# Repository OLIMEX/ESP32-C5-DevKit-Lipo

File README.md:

# ESP32-C5-DevKit-Lipo
Dual band 2.4Ghz and 5Ghz WiFi 6, Bluetooth 5 LE, Zigbee, Thread, Matter development board UEXT, USB programming, USB JTAG and LiPo battery UPS

https://www.olimex.com/Products/IoT/ESP32-C5/ESP32-C5-DevKit-Lipo/open-source-hardware

Features:

* 32 bit RISC-V processor 240Mhz
* Dual-Band Wi-Fi (2.4 GHz + 5 GHz)
* Bluetooth 5, Zigbee, Thread, Matter
* 8 MB Flash + 4 MB RAM
* UEXT connector
* USB-C (Power & Debug)
* USB-C JTAG
* Boot & Reset buttons
* Extension connector
* 0.9" (22.86 mm) space between the headers
* LiPo UPS charger & step-up converter
* Status LEDs
* Two mouting holes
* Dimensions 53x25mm

## Licenses

* Hardware is released under CERN Open Hardware Licence Version 2 - Strongly Reciprocal, all silkscreen credits to Olimex should remain;
* Software is released under MIT Licensee
* Documentation is released under CC BY-SA 4.0

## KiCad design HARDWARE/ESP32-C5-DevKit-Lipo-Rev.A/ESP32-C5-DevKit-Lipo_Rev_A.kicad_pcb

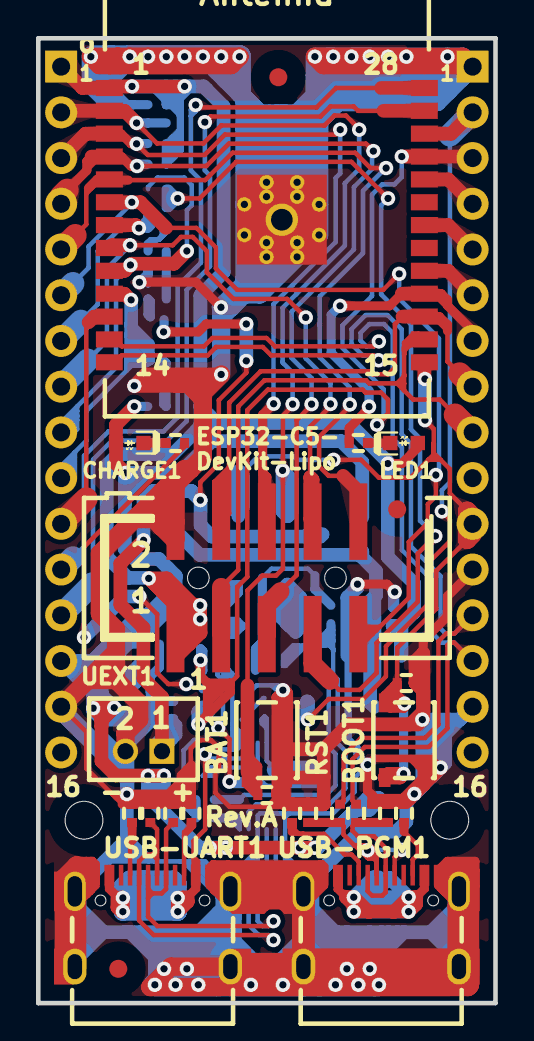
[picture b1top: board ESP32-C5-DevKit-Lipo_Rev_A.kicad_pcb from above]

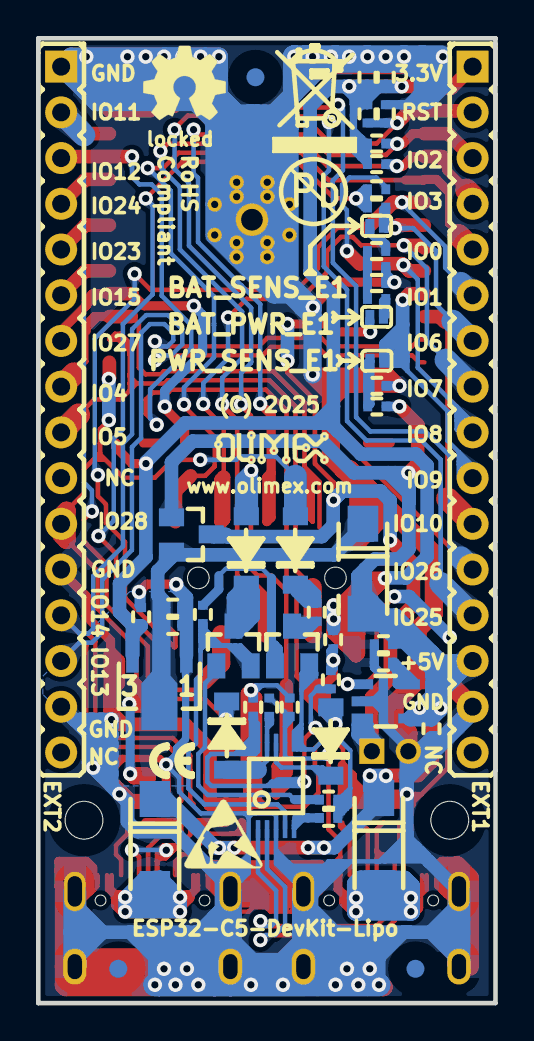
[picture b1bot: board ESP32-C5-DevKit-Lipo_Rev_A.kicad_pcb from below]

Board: 2 copper layers, 25.4 x 53.6 mm, 86 parts (56 on the bottom side), 58 nets.

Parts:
BAT1: DW02S; LIPO_BAT_VERTICAL_DW02S
BAT_PWR_E1: Opened; SJ_1_SMALLER
BAT_SENS_E1: Opened; SJ_1_SMALLER
BOOT1: YTS-A016-X
C1, C2, C7, C10, C12: 10uF/6.3V/20%/X5R/C0402; C_0402_5MIL_DWS
C3, C8, C11: 100nF/10V/20%/X5R/C0402; C_0402_5MIL_DWS
C4: 1uF/6.3V/10%/X5R/C0402; C_0402_5MIL_DWS
C5, C6: NA(150pF/50V/2%/NP0/C0402); C_0402_5MIL_DWS
C9: NA(10uF/6.3V/20%/X5R/C0402); C_0402_5MIL_DWS
C13, C14: NA(100nF/10V/20%/X5R/C0402); C_0402_5MIL_DWS
CHARGE1: LED/Yellow/0603; LED_0603_KA
D1, D2, D3: 1N5822/SS34/SMA; SMA-KA
D4, D5, D6, D7: 1N5819S4(SOD-123); SOD-123_1C-2A_KA
EXT1, EXT2: HN1x16
FET1: IRLML6402TRPbF; SOT23
FID1, FID2, FID5, FID6: Fiducial; Fiducial1x3
FID3, FID4: Fiducial; Fiducial1x3_Paste
LED1: LED/Green/0603; LED_0603_KA
Logo_OLIMEX_80: Logo_OLIMEX_80
MH1, MH2: Drill-2.1mm_Clerance-4mm; Mounting_Hole_Drill-2.1mm_Clerance-4mm
PWR_SENS_E1: Opened; SJ_1_SMALLER
R1, R2, R3, R5: 5.1k/1%/R0402; R_0402_5MIL_DWS
R4, R9, R10, R12, R13: 10k/R0402; R_0402_5MIL_DWS
R6, R7: 33R/R0402; R_0402_5MIL_DWS
R8, R11, R22, R27: 2.2k/R0402; R_0402_5MIL_DWS
R14, R21: 0R/R0402; R_0402_5MIL_DWS
R15: NA(0R/R0402); R_0402_5MIL_DWS
R16: 4.7k/R0402; R_0402_5MIL_DWS
R17, R18, R24: 470k/R0402; R_0402_5MIL_DWS
R19, R20: 1k/R0402; R_0402_5MIL_DWS
R23: 220k/R0402; R_0402_5MIL_DWS
R25: 220R/R0402; R_0402_5MIL_DWS
R26: NA(10k/R0402); R_0402_5MIL_DWS
RST1: YTS-A016-X
Sign_Antistatic_150: Sign_Antistatic_150
Sign_CE_Small: CE_Sign_Small
Sign_OSHW_7.3x6.0mm: Sign_OSHW_7.3x6.0mm; Sign_OSHW_7.3x6.0mmn
Sign_PB-Free: Sign_PB-Free
Sign_RecycleBin_1: Sign_RecycleBin_1
T1, T2: BC817-40(SOT23); SOT23
TVS1, TVS2, TVS3, TVS4: GG0402052R542P; D_0402_5MIL_DWS
U1: TP4054-42-SOT25-R; SOT-23-5
U2: CH340X(MSOP-10); MSOP-10_Pitch-0.5mm_3.00x3.00x1.00mm
U3: ESP32-C5-WROOM-1-N8R4; ESP32-C5-WROOM-1-N4-UNIVERSAL_MODULE
UEXT1: P-B-V-10-LF; GBH-254-SMT-10
USB-PGM1: USB-C-16P-F(A40-00119-A52-12); USB2.0_TYPE-C(A40-00119-A52-12)_Paste
USB-UART1: USB-C-16P-F(A40-00119-A52-12); USB2.0_TYPE-C(A40-00119-A52-12)_Paste
VR1: WL9005P3-33(SOT89-3); SOT89-3

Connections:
+3.3V: C2.2, C3.1, C12.1, EXT1.1, LED1.2 (A), R4.2, R11.1, R22.2, R26.2, U3.2 (3V3), UEXT1.1, VR1.3 (VOUT)
+5V: C1.1, CHARGE1.2 (A), D1.1 (K), D2.1 (K), D3.2 (A), EXT1.14, FET1.1, R10.1, R23.1, U1.4 (VCC)
+5V_USB: D1.2 (A), USB-PGM1.A4 (VBUS), USB-PGM1.A9 (VBUS), USB-PGM1.B4 (VBUS), USB-PGM1.B9 (VBUS)
/D+: TVS3.1 (IO1), U2.1 (UD+), USB-UART1.A6 (DP1), USB-UART1.B6 (DP2)
/D-: TVS4.1 (IO1), U2.2 (UD-), USB-UART1.A7 (DN1), USB-UART1.B7 (DN2)
/ESP_EN: C4.2, C13.1, D6.2 (A), EXT1.2, R4.1, RST1.1, U3.3 (EN)
/GPIO0\SPI2_CS: EXT1.5, U3.6 (IO0/GPIO0/XTAL_32K_P/LP_GPIO0/LP_UART_D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), UEXT1.10
/GPIO1\SPI2_CLK: EXT1.6, U3.7 (IO1/GPIO1/XTAL_32K_N/LP_GPIO1/LP_UART_D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), UEXT1.9
/GPIO2\LP_I2C_SDA\I2C_SDA: EXT1.3, R22.1, U3.4 (IO2/MTMS/GPIO2/LP_GPIO2/LP_UART_RTSN/LP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), UEXT1.6
/GPIO3\LP_I2C_SCL\I2C_SCL: EXT1.4, R11.2, U3.5 (IO3/MTDI/GPIO3/LP_GPIO3/LP_UART_CTSN/LP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), UEXT1.5
/GPIO4\LP_UART_RXD\U1RXD: EXT2.8, U3.17 (IO4/MTCK/GPIO4/LP_GPIO4/LP_UART_RXD/ADC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), UEXT1.4
/GPIO5\LP_UART_TXD\U1TXD: EXT2.9, U3.16 (IO5/MTDO/GPIO5/LP_GPIO5/LP_UART_TXD/ADC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), UEXT1.3
/GPIO6\SPI2_MISO\ADC1_CH5: BAT_SENS_E1.2, EXT1.7, R15.2, U3.8 (IO6/GPIO6/LP_GPIO6/ADC1_CH5/FSPICLK)
/GPIO7\SPI2_MOSI: EXT1.8, U3.9 (IO7/GPIO7/LP_GPIO7/FSPID/SDIO_DATA1), UEXT1.8
/GPIO8\SPI2_MISO: EXT1.9, R14.2, U3.10 (IO8/GPIO8/PAD_COMP0/SDIO_DATA0)
/GPIO9\PWR_SENS: EXT1.10, PWR_SENS_E1.2, U3.11 (IO9/GPIO9/PAD_COMP1/SDIO_CLK)
/GPIO10: EXT1.11, U3.12 (IO10/GPIO10/FSPICS0/SDIO_CMD)
/GPIO11\U0TXD: D5.1 (K), EXT2.2, U3.25 (IO11/U0TXD/GPIO11)
/GPIO12\U0RXD: D4.2 (A), EXT2.3, R13.2, R26.1, U3.24 (IO12/U0RXD/GPIO12)
/GPIO23: EXT2.5, U3.21 (IO23/GPIO23)
/GPIO24: EXT2.4, U3.23 (IO24/GPIO24)
/GPIO25: EXT1.13, U3.26 (IO25/GPIO25)
/GPIO26: EXT1.12, U3.27 (IO26/GPIO26)
/GPIO27\USER_LED1: EXT2.7, R27.2, U3.18 (IO27/GPIO27)
/GPIO28\BOOT: BOOT1.1, C14.1, D7.2 (A), EXT2.11, U3.15 (IO28/GPIO28)
/NC_GPIO15: EXT2.6, U3.19 (NC/SPICS1/GPIO15)
/USB_D+: C5.1, R7.2, TVS1.1 (IO1), USB-PGM1.A6 (DP1), USB-PGM1.B6 (DP2)
/USB_D-: C6.1, R6.1, TVS2.1 (IO1), USB-PGM1.A7 (DN1), USB-PGM1.B7 (DN2)
/USB_DN: EXT2.14, R6.2, U3.13 (IO13/GPIO13/USB_D-/SDIO_DATA3)
/USB_DP: EXT2.13, R7.1, U3.14 (IO14/GPIO14/USB_D+/SDIO_DATA2)
/V3: C8.1, R13.1, U2.10 (V3)
/Vin: C9.1, C10.1, D3.1 (K), FET1.2, VR1.2 (VIN)
GND: BAT1.2, BOOT1.2, C1.2, C2.1, C3.2, C4.1, C5.2, C6.2, C7.1, C8.2, C9.2, C10.2, C11.1, C12.2, C13.2, C14.2, EXT1.15, EXT2.1, EXT2.12, EXT2.15, R1.1, R2.1, R3.1, R5.1, R9.1, R10.2, R18.2, R24.2, RST1.2, TVS1.2 (IO2), TVS2.2 (IO2), TVS3.2 (IO2), TVS4.2 (IO2), U1.2 (GND), U2.3 (GND), U3.1 (GND), U3.28 (GND), U3.29 (EPAD), UEXT1.2, USB-PGM1.0 (SHELL), USB-PGM1.A1 (GND), USB-PGM1.A12 (GND), USB-PGM1.B1 (GND), USB-PGM1.B12 (GND), USB-UART1.0 (SHELL), USB-UART1.A1 (GND), USB-UART1.A12 (GND), USB-UART1.B1 (GND), USB-UART1.B12 (GND), VR1.1 (GND)
unnamed: BAT_PWR_E1.1, R17.1
unnamed: BAT_SENS_E1.1, R21.2
unnamed: C11.2, R17.2, R18.1, R21.1
unnamed: CHARGE1.1 (K), R8.2
unnamed: D4.1 (K), U2.8 (TXD)
unnamed: D5.2 (A), R12.2, U2.9 (RXD)
unnamed: D6.1 (K), T1.3 (C)
unnamed: D7.1 (K), R25.2
unnamed: LED1.1 (K), R27.1
unnamed: PWR_SENS_E1.1, R23.2, R24.1
unnamed: R14.1, R15.1, UEXT1.7
unnamed: R19.2, T1.1 (B)
unnamed: R20.1, T1.2 (E), U2.4 (RTS#)
unnamed: R20.2, T2.1 (B)
unnamed: R25.1, T2.3 (C)
unnamed: R16.1, R19.1, T2.2 (E), U2.6 (TNOW/DTR#)
unnamed: R8.1, U1.1 (CHRGb)
unnamed: R9.2, U1.5 (PROG)
unnamed: R16.2, U2.5 (CTS#)
unnamed: R2.2, USB-PGM1.A5 (CC1)
unnamed: R1.2, USB-PGM1.B5 (CC2)
unnamed: R5.2, USB-UART1.A5 (CC1)
unnamed: R3.2, USB-UART1.B5 (CC2)
VBAT: BAT1.1, BAT_PWR_E1.2, FET1.3, U1.3 (VBAT)
VBUS: C7.2, D2.2 (A), R12.1, U2.7 (VCC), USB-UART1.A4 (VBUS), USB-UART1.A9 (VBUS), USB-UART1.B4 (VBUS), USB-UART1.B9 (VBUS)

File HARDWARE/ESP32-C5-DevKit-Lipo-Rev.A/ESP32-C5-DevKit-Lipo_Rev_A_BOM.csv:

"Id";"Designator";"Footprint";"Quantity";"Designation";"Supplier and ref";
1;"BOOT1,RST1";"YTS-A016-X";2;"YTS-A016-X";;;
2;"LED1";"LED_0603_KA";1;"LED/Green/0603";;;
3;"MH1,MH2";"Mounting_Hole_Drill-2.1mm_Clerance-4mm";2;"Drill-2.1mm_Clerance-4mm";;;
4;"CHARGE1";"LED_0603_KA";1;"LED/Yellow/0603";;;
5;"BAT1";"LIPO_BAT_VERTICAL_DW02S";1;"DW02S";;;
6;"R6,R7";"R_0402_5MIL_DWS";2;"33R/R0402";;;
7;"C13,C14";"C_0402_5MIL_DWS";2;"NA(100nF/10V/20%/X5R/C0402)";;;
8;"FID3,FID4";"Fiducial1x3_Paste";2;"Fiducial";;;
9;"R2,R5,R1,R3";"R_0402_5MIL_DWS";4;"5.1k/1%/R0402";;;
10;"U3";"ESP32-C5-WROOM-1-N4-UNIVERSAL_MODULE";1;"ESP32-C5-WROOM-1-N8R4";;;
11;"UEXT1";"GBH-254-SMT-10";1;"P-B-V-10-LF";;;
12;"R27,R8,R11,R22";"R_0402_5MIL_DWS";4;"2.2k/R0402";;;
13;"TVS4,TVS2,TVS1,TVS3";"D_0402_5MIL_DWS";4;"GG0402052R542P";;;
14;"USB-UART1,USB-PGM1";"USB2.0_TYPE-C(A40-00119-A52-12)_Paste";2;"USB-C-16P-F(A40-00119-A52-12)";;;
15;"C6,C5";"C_0402_5MIL_DWS";2;"NA(150pF/50V/2%/NP0/C0402)";;;
16;"FID1,FID2,FID5,FID6";"Fiducial1x3";4;"Fiducial";;;
17;"R18,R17,R24";"R_0402_5MIL_DWS";3;"470k/R0402";;;
18;"R10,R9,R4,R13,R12";"R_0402_5MIL_DWS";5;"10k/R0402";;;
19;"D3,D2,D1";"SMA-KA";3;"1N5822/SS34/SMA";;;
20;"C11,C8,C3";"C_0402_5MIL_DWS";3;"100nF/10V/20%/X5R/C0402";;;
21;"D7,D5,D6,D4";"SOD-123_1C-2A_KA";4;"1N5819S4(SOD-123)";;;
22;"U2";"MSOP-10_Pitch-0.5mm_3.00x3.00x1.00mm";1;"CH340X(MSOP-10)";;;
23;"R19,R20";"R_0402_5MIL_DWS";2;"1k/R0402";;;
24;"R16";"R_0402_5MIL_DWS";1;"4.7k/R0402";;;
25;"PWR_SENS_E1,BAT_SENS_E1,BAT_PWR_E1";"SJ_1_SMALLER";3;"Opened";;;
26;"T2,T1";"SOT23";2;"BC817-40(SOT23)";;;
27;"R21,R14";"R_0402_5MIL_DWS";2;"0R/R0402";;;
28;"U1";"SOT-23-5";1;"TP4054-42-SOT25-R";;;
29;"C7,C12,C10,C2,C1";"C_0402_5MIL_DWS";5;"10uF/6.3V/20%/X5R/C0402";;;
30;"C9";"C_0402_5MIL_DWS";1;"NA(10uF/6.3V/20%/X5R/C0402)";;;
31;"R25";"R_0402_5MIL_DWS";1;"220R/R0402";;;
32;"C4";"C_0402_5MIL_DWS";1;"1uF/6.3V/10%/X5R/C0402";;;
33;"EXT1,EXT2";"HN1x16";2;"HN1x16";;;
34;"VR1";"SOT89-3";1;"WL9005P3-33(SOT89-3)";;;
35;"R23";"R_0402_5MIL_DWS";1;"220k/R0402";;;
36;"R15";"R_0402_5MIL_DWS";1;"NA(0R/R0402)";;;
37;"R26";"R_0402_5MIL_DWS";1;"NA(10k/R0402)";;;
38;"FET1";"SOT23";1;"IRLML6402TRPbF";;;

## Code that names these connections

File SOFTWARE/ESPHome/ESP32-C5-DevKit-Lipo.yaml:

esphome:
  name: esp32-c5-devkit-lipo
  friendly_name: ESP32-C5-DevKit-Lipo

esp32:
  board: esp32-c5-devkitc-1
  variant: esp32c5
  framework:
    type: arduino

psram:
  mode: opi

# ============================================================
# LOGGING / CONTROL (Native USB)
# ============================================================
logger:

api:
ota:
captive_portal:

wifi:
  ssid: "YOUR_SSID"
  password: "YOUR_PASSWORD"
  ap:
    ssid: "ESP32-C5-DevKit-Lipo Fallback"
    password: "12345678"

# ============================================================
# USER LED — GPIO27
# ============================================================
output:
  - platform: gpio
    pin: GPIO27
    id: user_led_output

light:
  - platform: binary
    name: "ESP32-C5-DevKit-Lipo User LED"
    output: user_led_output

# ============================================================
# BOOT BUTTON — GPIO28
# ============================================================
binary_sensor:
  - platform: gpio
    name: "ESP32-C5-DevKit-Lipo Boot Button"
    pin:
      number: GPIO28
      mode:
        input: true
        pullup: true
      inverted: true
    on_press:
      - light.toggle: user_led_output

# ============================================================
# UEXT I2C — GPIO3 SCL / GPIO2 SDA
# ============================================================
i2c:
  sda: GPIO2
  scl: GPIO3
  scan: true

# ============================================================
# UEXT SPI BUS
# ============================================================
spi:
  clk_pin: GPIO1
  mosi_pin: GPIO7
  miso_pin: GPIO8

# Chip select available:
# GPIO0

# ============================================================
# UEXT UART — GPIO5 TX / GPIO4 RX
# ============================================================
uart:
  - id: uext_uart
    tx_pin: GPIO5
    rx_pin: GPIO4
    baud_rate: 115200

# ============================================================
# CH340 USB-UART (GPIO11 TX / GPIO12 RX)
# DO NOT use these pins for peripherals
# ============================================================

# ============================================================
# OPTIONAL — BATTERY VOLTAGE (GPIO6)
# Enable only if jumpers BAT_PWR_E1 and BAT_SENSE_E1 are closed
# ============================================================
# sensor:
#   - platform: adc
#     pin: GPIO6
#     name: "ESP32-C5-DevKit-Lipo Battery Voltage"
#     attenuation: 11db
#     update_interval: 30s
#     unit_of_measurement: "V"
#     accuracy_decimals: 2
#     device_class: voltage
#     state_class: measurement

# ============================================================
# OPTIONAL — EXTERNAL POWER SENSE (GPIO9)
# Enable only if jumper PWR_SENS_E1 is closed
# ============================================================
# binary_sensor:
#   - platform: gpio
#     name: "ESP32-C5-DevKit-Lipo External Power"
#     pin:
#       number: GPIO9
#       mode: input

# ============================================================
# HARDWARE NOTES — ESP32-C5-DevKit-Lipo
# ============================================================
# Native USB is active by default.
# CH340 USB uses:
#   TX = GPIO11
#   RX = GPIO12
#
# Do not attach peripherals to GPIO11/12 if using CH340.
#
# GPIO0 is SPI CS — avoid pulling LOW at boot.
# GPIO28 is boot button.
# ESP_EN is hardware reset (not GPIO).
#
# 8MB Flash / 4MB PSRAM (OPI mode).

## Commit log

2025-11-11 initial upload
2025-11-12 Update
    New demos
2025-11-13 Update
    New UEXT demo with MOD-IR-TEMP sensor
2025-11-14 Update
    New demo with MOD-L3GD20 3-axis gyroscope
2025-11-14 Update
    ESP-IDF demo
2025-11-17 Update
    Improved battery measurement circuit before board release
2025-11-19 Update
    New battery sense and battery voltage demo
2026-02-13 Update
    Added json and yaml
2026-04-24 Update olimex_esp32-c5-devkit-lipo.json
    Edited a couple of mistakes based on customer feedback

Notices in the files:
HARDWARE/ESP32-C5-DevKit-Lipo-Rev.A/ESP32-C5-DevKit-Lipo_Rev_A.kicad_pcb:
(C) 2025
